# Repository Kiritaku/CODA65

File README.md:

# CODA65
 A 65% keyboard with split arrow keys, rotary encoder, and underglow

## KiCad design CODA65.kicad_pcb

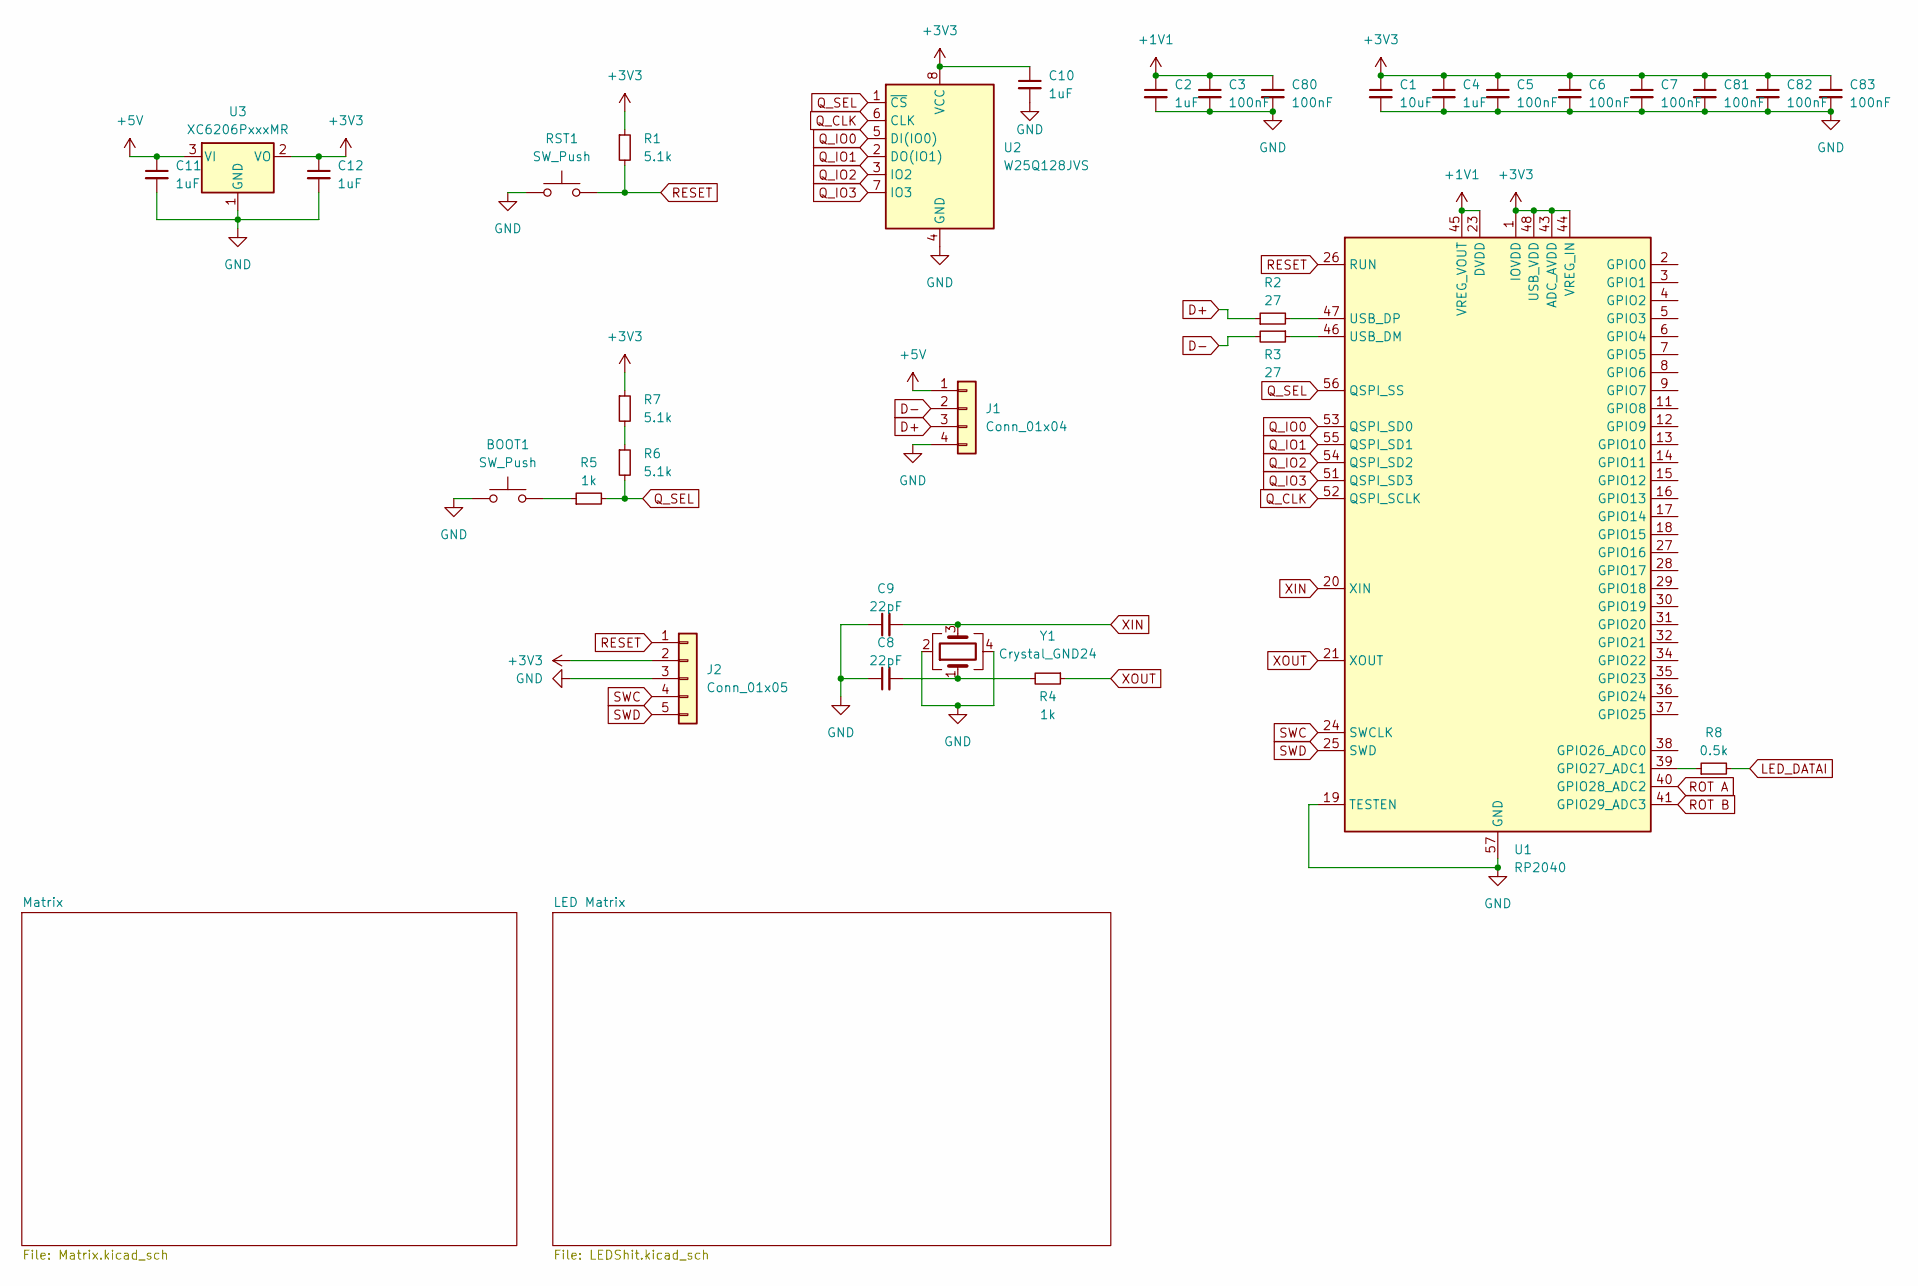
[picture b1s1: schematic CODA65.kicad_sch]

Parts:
BOOT1: SW_Push; SW_Push_1P1T_XKB_TS-1187A
C1: 10uF; C_0603_1608Metric
C2, C4, C10, C11, C12: 1uF; C_0402_1005Metric
C3, C5, C6, C7, C80, C81, C82, C83: 100nF; C_0402_1005Metric
C8, C9: 22pF; C_0402_1005Metric
J1: Conn_01x04; JST_SH_SM04B-SRSS-TB_1x04-1MP_P1.00mm_Horizontal
J2: Conn_01x05; PinHeader_1x05_P2.54mm_Vertical
R1, R6, R7: 5.1k; R_0402_1005Metric
R2, R3: 27; R_0402_1005Metric
R4, R5: 1k; R_0402_1005Metric
R8: 0.5k; R_0402_1005Metric
RST1: SW_Push; SW_Push_1P1T_XKB_TS-1187A
U1: RP2040; QFN-56-1EP_7x7mm_P0.4mm_EP3.2x3.2mm
U2: W25Q128JVS; SOIC-8_5.23x5.23mm_P1.27mm
U3: XC6206PxxxMR; SOT-23-3
Y1: Crystal_GND24; Crystal_SMD_3225-4Pin_3.2x2.5mm

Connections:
+1V1: C2.1, C3.1, C80.1, U1.23 (DVDD), U1.45 (VREG_VOUT), U1.50 (DVDD)
+3V3: C1.1, C4.1, C5.1, C6.1, C7.1, C10.1, C12.1, C81.1, C82.1, C83.1, J2.2, R1.1, R7.1, U1.1 (IOVDD), U1.10 (IOVDD), U1.22 (IOVDD), U1.33 (IOVDD), U1.42 (IOVDD), U1.43 (ADC_AVDD), U1.44 (VREG_IN), U1.48 (USB_VDD), U1.49 (IOVDD), U2.8 (VCC), U3.2 (VO)
+5V: C11.1, J1.1, U3.3 (VI); also elsewhere on the board
D+: J1.3, R2.1
D-: J1.2, R3.2
GND: BOOT1.1, C1.2, C2.2, C3.2, C4.2, C5.2, C6.2, C7.2, C8.1, C9.1, C10.2, C11.2, C12.2, C80.2, C81.2, C82.2, C83.2, J1.4, J2.3, RST1.1, U1.19 (TESTEN), U1.57 (GND), U2.4 (GND), U3.1 (GND), Y1.2, Y1.4; also elsewhere on the board
LED_DATAI: R8.2; also elsewhere on the board
unnamed: BOOT1.2, R5.1
unnamed: C8.2, R4.2, Y1.1
unnamed: R6.1, R7.2
unnamed: R8.1, U1.39 (GPIO27_ADC1)
unnamed: R3.1, U1.46 (USB_DM)
unnamed: R2.2, U1.47 (USB_DP)
Q_CLK: U1.52 (QSPI_SCLK), U2.6 (CLK)
Q_IO0: U1.53 (QSPI_SD0), U2.5 (DI(IO0))
Q_IO1: U1.55 (QSPI_SD1), U2.2 (DO(IO1))
Q_IO2: U1.54 (QSPI_SD2), U2.3 (IO2)
Q_IO3: U1.51 (QSPI_SD3), U2.7 (IO3)
Q_SEL: R5.2, R6.2, U1.56 (QSPI_SS), U2.1 (~CS)
RESET: J2.1, R1.2, RST1.2, U1.26 (RUN)
ROT A: U1.40 (GPIO28_ADC2); also elsewhere on the board
ROT B: U1.41 (GPIO29_ADC3); also elsewhere on the board
SWC: J2.4, U1.24 (SWCLK)
SWD: J2.5, U1.25 (SWD)
XIN: C9.2, U1.20 (XIN), Y1.3
XOUT: R4.1, U1.21 (XOUT)

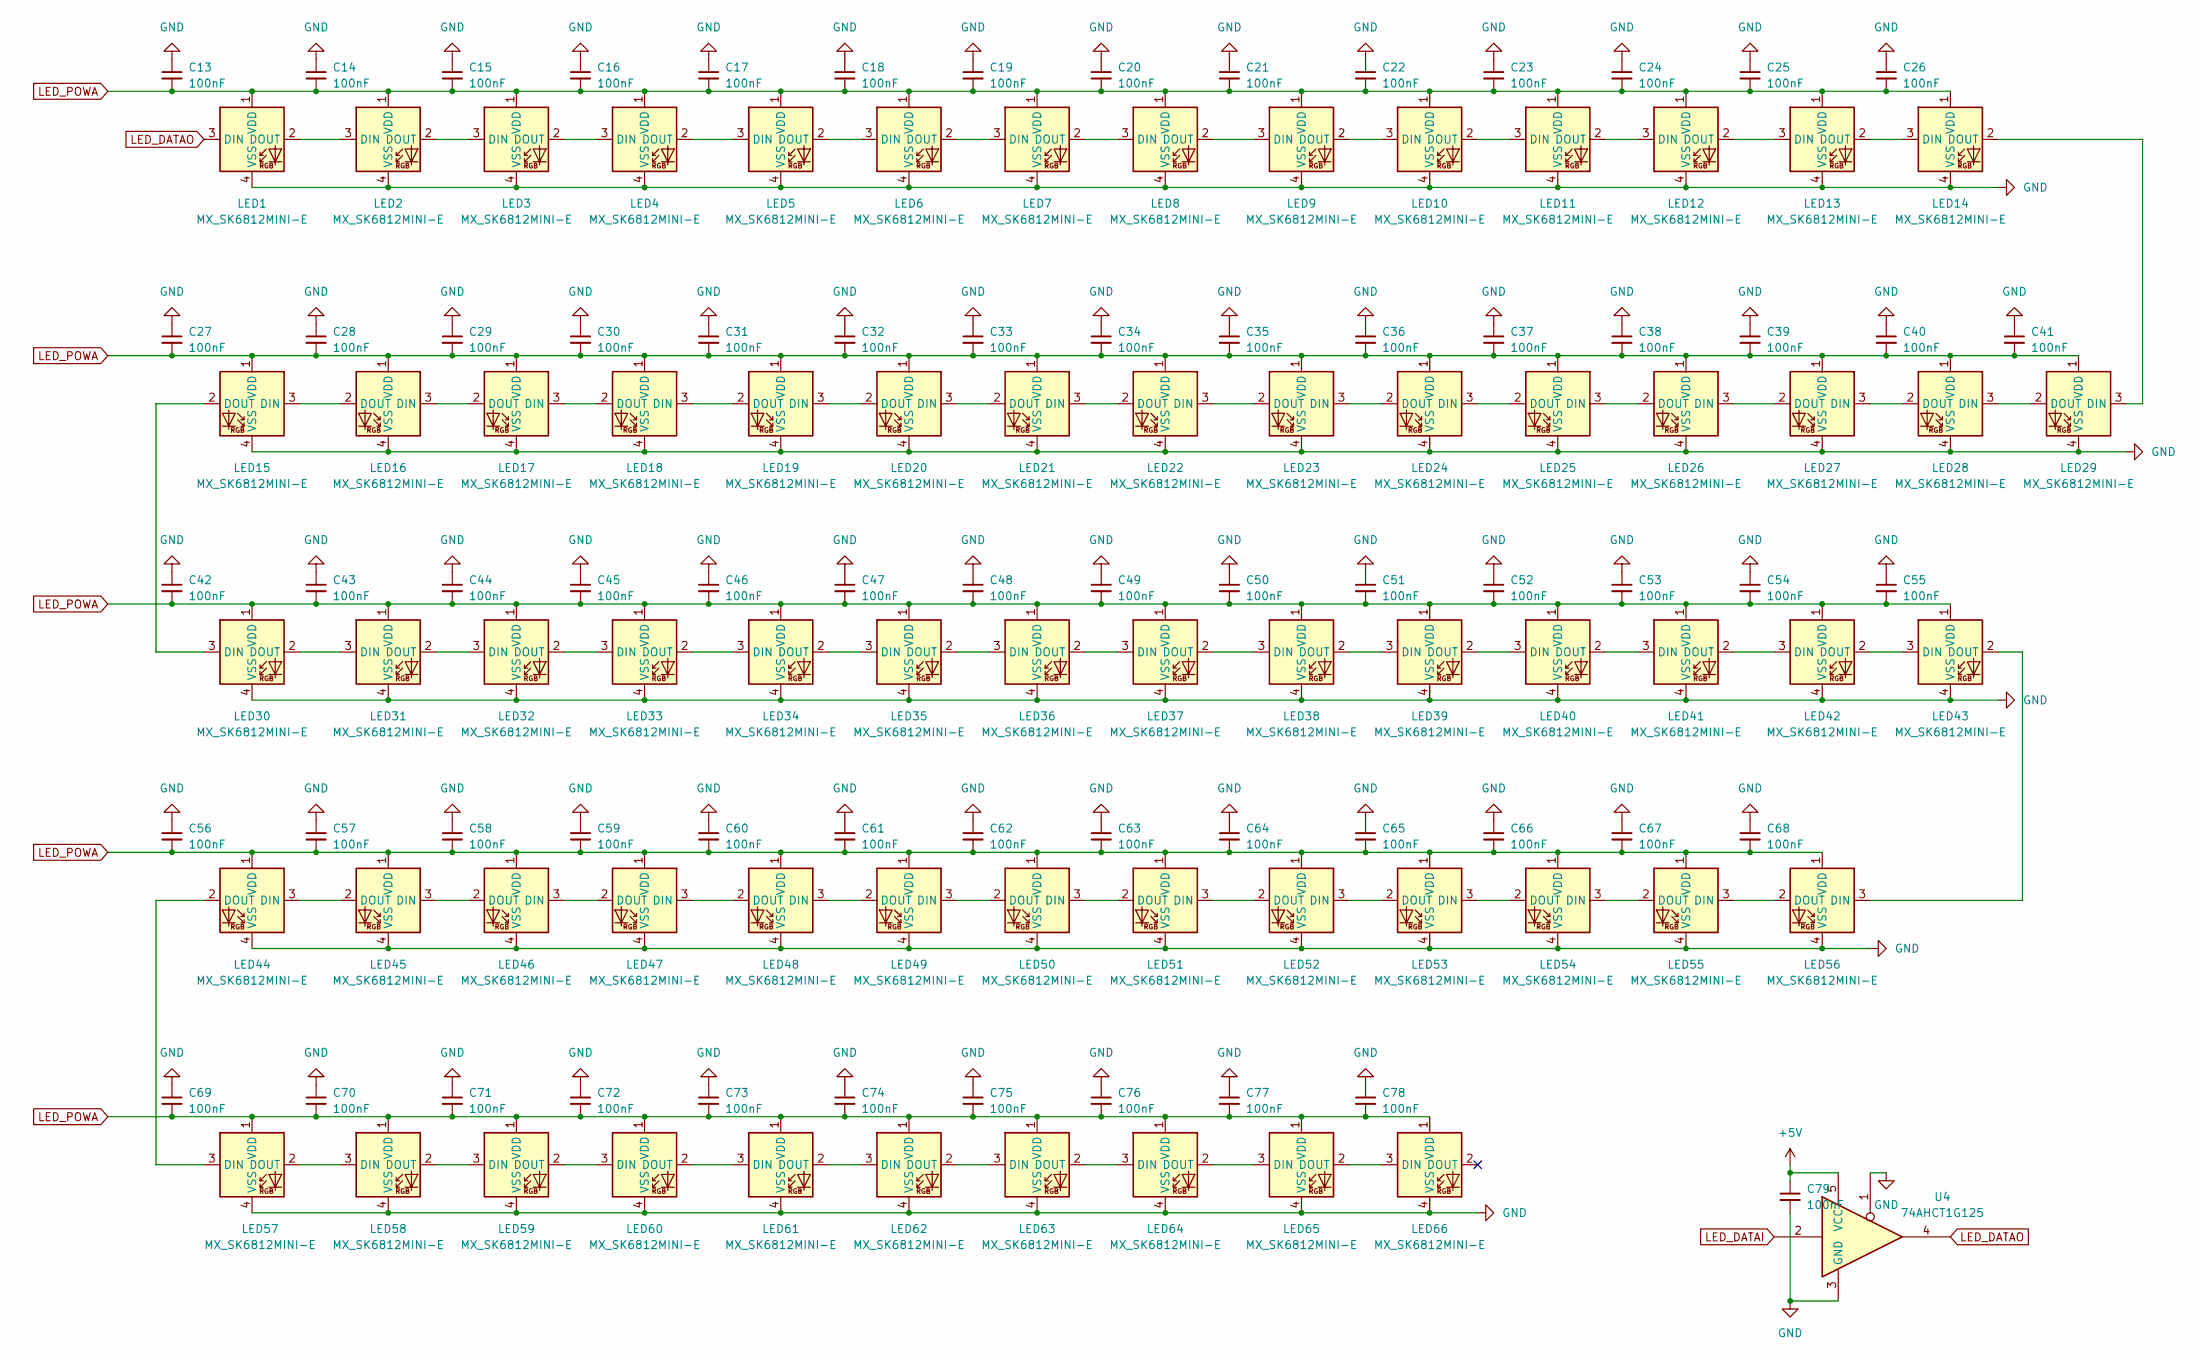
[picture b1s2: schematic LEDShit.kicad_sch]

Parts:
C13, C14, C15, C16, C17, C18, C19, C20, C21, C22, C23, C24, C25, C26, C27, C28, C29, C30, C31, C32, C33, C34, C35, C36, C37, C38, C39, C40, C41, C42, C43, C44, C45, C46, C47, C48, C49, C50, C51, C52, C53, C54, C55, C56, C57, C58, C59, C60, C61, C62, C63, C64, C65, C66, C67, C68, C69, C70, C71, C72, C73, C74, C75, C76, C77, C78, C79: 100nF; C_0402_1005Metric
LED1, LED2, LED3, LED4, LED5, LED6, LED7, LED8, LED9, LED10, LED11, LED12, LED13, LED14, LED15, LED16, LED17, LED18, LED19, LED20, LED21, LED22, LED23, LED24, LED25, LED26, LED27, LED28, LED29, LED30, LED31, LED32, LED33, LED34, LED35, LED36, LED37, LED38, LED39, LED40, LED41, LED42, LED43, LED44, LED45, LED46, LED47, LED48, LED49, LED50, LED51, LED52, LED53, LED54, LED55, LED56, LED57, LED58, LED59, LED60, LED61, LED62, LED63, LED64, LED65, LED66: MX_SK6812MINI-E; LED_MX_6028R
U4: 74AHCT1G125; SOT-23-5

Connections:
+5V: C79.1, U4.5 (VCC); also elsewhere on the board
GND: C13.1, C14.1, C15.1, C16.1, C17.1, C18.1, C19.1, C20.1, C21.1, C22.1, C23.1, C24.1, C25.1, C26.1, C27.1, C28.1, C29.1, C30.1, C31.1, C32.1, C33.1, C34.1, C35.1, C36.1, C37.1, C38.1, C39.1, C40.1, C41.1, C42.1, C43.1, C44.1, C45.1, C46.1, C47.1, C48.1, C49.1, C50.1, C51.1, C52.1, C53.1, C54.1, C55.1, C56.1, C57.1, C58.1, C59.1, C60.1, C61.1, C62.1, C63.1, C64.1, C65.1, C66.1, C67.1, C68.1, C69.1, C70.1, C71.1, C72.1, C73.1, C74.1, C75.1, C76.1, C77.1, C78.1, C79.2, LED1.4 (VSS), LED2.4 (VSS), LED3.4 (VSS), LED4.4 (VSS), LED5.4 (VSS), LED6.4 (VSS), LED7.4 (VSS), LED8.4 (VSS), LED9.4 (VSS), LED10.4 (VSS), LED11.4 (VSS), LED12.4 (VSS), LED13.4 (VSS), LED14.4 (VSS), LED15.4 (VSS), LED16.4 (VSS), LED17.4 (VSS), LED18.4 (VSS), LED19.4 (VSS), LED20.4 (VSS), LED21.4 (VSS), LED22.4 (VSS), LED23.4 (VSS), LED24.4 (VSS), LED25.4 (VSS), LED26.4 (VSS), LED27.4 (VSS), LED28.4 (VSS), LED29.4 (VSS), LED30.4 (VSS), LED31.4 (VSS), LED32.4 (VSS), LED33.4 (VSS), LED34.4 (VSS), LED35.4 (VSS), LED36.4 (VSS), LED37.4 (VSS), LED38.4 (VSS), LED39.4 (VSS), LED40.4 (VSS), LED41.4 (VSS), LED42.4 (VSS), LED43.4 (VSS), LED44.4 (VSS), LED45.4 (VSS), LED46.4 (VSS), LED47.4 (VSS), LED48.4 (VSS), LED49.4 (VSS), LED50.4 (VSS), LED51.4 (VSS), LED52.4 (VSS), LED53.4 (VSS), LED54.4 (VSS), LED55.4 (VSS), LED56.4 (VSS), LED57.4 (VSS), LED58.4 (VSS), LED59.4 (VSS), LED60.4 (VSS), LED61.4 (VSS), LED62.4 (VSS), LED63.4 (VSS), LED64.4 (VSS), LED65.4 (VSS), LED66.4 (VSS), U4.1, U4.3 (GND); also elsewhere on the board
LED_DATAI: U4.2; also elsewhere on the board
LED_DATAO: LED1.3 (DIN), U4.4
LED_POWA: C13.2, C14.2, C15.2, C16.2, C17.2, C18.2, C19.2, C20.2, C21.2, C22.2, C23.2, C24.2, C25.2, C26.2, C27.2, C28.2, C29.2, C30.2, C31.2, C32.2, C33.2, C34.2, C35.2, C36.2, C37.2, C38.2, C39.2, C40.2, C41.2, C42.2, C43.2, C44.2, C45.2, C46.2, C47.2, C48.2, C49.2, C50.2, C51.2, C52.2, C53.2, C54.2, C55.2, C56.2, C57.2, C58.2, C59.2, C60.2, C61.2, C62.2, C63.2, C64.2, C65.2, C66.2, C67.2, C68.2, C69.2, C70.2, C71.2, C72.2, C73.2, C74.2, C75.2, C76.2, C77.2, C78.2, LED1.1 (VDD), LED2.1 (VDD), LED3.1 (VDD), LED4.1 (VDD), LED5.1 (VDD), LED6.1 (VDD), LED7.1 (VDD), LED8.1 (VDD), LED9.1 (VDD), LED10.1 (VDD), LED11.1 (VDD), LED12.1 (VDD), LED13.1 (VDD), LED14.1 (VDD), LED15.1 (VDD), LED16.1 (VDD), LED17.1 (VDD), LED18.1 (VDD), LED19.1 (VDD), LED20.1 (VDD), LED21.1 (VDD), LED22.1 (VDD), LED23.1 (VDD), LED24.1 (VDD), LED25.1 (VDD), LED26.1 (VDD), LED27.1 (VDD), LED28.1 (VDD), LED29.1 (VDD), LED30.1 (VDD), LED31.1 (VDD), LED32.1 (VDD), LED33.1 (VDD), LED34.1 (VDD), LED35.1 (VDD), LED36.1 (VDD), LED37.1 (VDD), LED38.1 (VDD), LED39.1 (VDD), LED40.1 (VDD), LED41.1 (VDD), LED42.1 (VDD), LED43.1 (VDD), LED44.1 (VDD), LED45.1 (VDD), LED46.1 (VDD), LED47.1 (VDD), LED48.1 (VDD), LED49.1 (VDD), LED50.1 (VDD), LED51.1 (VDD), LED52.1 (VDD), LED53.1 (VDD), LED54.1 (VDD), LED55.1 (VDD), LED56.1 (VDD), LED57.1 (VDD), LED58.1 (VDD), LED59.1 (VDD), LED60.1 (VDD), LED61.1 (VDD), LED62.1 (VDD), LED63.1 (VDD), LED64.1 (VDD), LED65.1 (VDD), LED66.1 (VDD)
unnamed: LED1.2 (DOUT), LED2.3 (DIN)
unnamed: LED2.2 (DOUT), LED3.3 (DIN)
unnamed: LED3.2 (DOUT), LED4.3 (DIN)
unnamed: LED4.2 (DOUT), LED5.3 (DIN)
unnamed: LED5.2 (DOUT), LED6.3 (DIN)
unnamed: LED6.2 (DOUT), LED7.3 (DIN)
unnamed: LED7.2 (DOUT), LED8.3 (DIN)
unnamed: LED8.2 (DOUT), LED9.3 (DIN)
unnamed: LED9.2 (DOUT), LED10.3 (DIN)
unnamed: LED10.2 (DOUT), LED11.3 (DIN)
unnamed: LED11.2 (DOUT), LED12.3 (DIN)
unnamed: LED12.2 (DOUT), LED13.3 (DIN)
unnamed: LED13.2 (DOUT), LED14.3 (DIN)
unnamed: LED14.2 (DOUT), LED29.3 (DIN)
unnamed: LED15.3 (DIN), LED16.2 (DOUT)
unnamed: LED15.2 (DOUT), LED30.3 (DIN)
unnamed: LED16.3 (DIN), LED17.2 (DOUT)
unnamed: LED17.3 (DIN), LED18.2 (DOUT)
unnamed: LED18.3 (DIN), LED19.2 (DOUT)
unnamed: LED19.3 (DIN), LED20.2 (DOUT)
unnamed: LED20.3 (DIN), LED21.2 (DOUT)
unnamed: LED21.3 (DIN), LED22.2 (DOUT)
unnamed: LED22.3 (DIN), LED23.2 (DOUT)
unnamed: LED23.3 (DIN), LED24.2 (DOUT)
unnamed: LED24.3 (DIN), LED25.2 (DOUT)
unnamed: LED25.3 (DIN), LED26.2 (DOUT)
unnamed: LED26.3 (DIN), LED27.2 (DOUT)
unnamed: LED27.3 (DIN), LED28.2 (DOUT)
unnamed: LED28.3 (DIN), LED29.2 (DOUT)
unnamed: LED30.2 (DOUT), LED31.3 (DIN)
unnamed: LED31.2 (DOUT), LED32.3 (DIN)
unnamed: LED32.2 (DOUT), LED33.3 (DIN)
unnamed: LED33.2 (DOUT), LED34.3 (DIN)
unnamed: LED34.2 (DOUT), LED35.3 (DIN)
unnamed: LED35.2 (DOUT), LED36.3 (DIN)
unnamed: LED36.2 (DOUT), LED37.3 (DIN)
unnamed: LED37.2 (DOUT), LED38.3 (DIN)
unnamed: LED38.2 (DOUT), LED39.3 (DIN)
unnamed: LED39.2 (DOUT), LED40.3 (DIN)
unnamed: LED40.2 (DOUT), LED41.3 (DIN)
unnamed: LED41.2 (DOUT), LED42.3 (DIN)
unnamed: LED42.2 (DOUT), LED43.3 (DIN)
unnamed: LED43.2 (DOUT), LED56.3 (DIN)
unnamed: LED44.3 (DIN), LED45.2 (DOUT)
unnamed: LED44.2 (DOUT), LED57.3 (DIN)
unnamed: LED45.3 (DIN), LED46.2 (DOUT)
unnamed: LED46.3 (DIN), LED47.2 (DOUT)
unnamed: LED47.3 (DIN), LED48.2 (DOUT)
unnamed: LED48.3 (DIN), LED49.2 (DOUT)
unnamed: LED49.3 (DIN), LED50.2 (DOUT)
unnamed: LED50.3 (DIN), LED51.2 (DOUT)
unnamed: LED51.3 (DIN), LED52.2 (DOUT)
unnamed: LED52.3 (DIN), LED53.2 (DOUT)
unnamed: LED53.3 (DIN), LED54.2 (DOUT)
unnamed: LED54.3 (DIN), LED55.2 (DOUT)
unnamed: LED55.3 (DIN), LED56.2 (DOUT)
unnamed: LED57.2 (DOUT), LED58.3 (DIN)
unnamed: LED58.2 (DOUT), LED59.3 (DIN)
unnamed: LED59.2 (DOUT), LED60.3 (DIN)
unnamed: LED60.2 (DOUT), LED61.3 (DIN)
unnamed: LED61.2 (DOUT), LED62.3 (DIN)
unnamed: LED62.2 (DOUT), LED63.3 (DIN)
unnamed: LED63.2 (DOUT), LED64.3 (DIN)
unnamed: LED64.2 (DOUT), LED65.3 (DIN)
unnamed: LED65.2 (DOUT), LED66.3 (DIN)

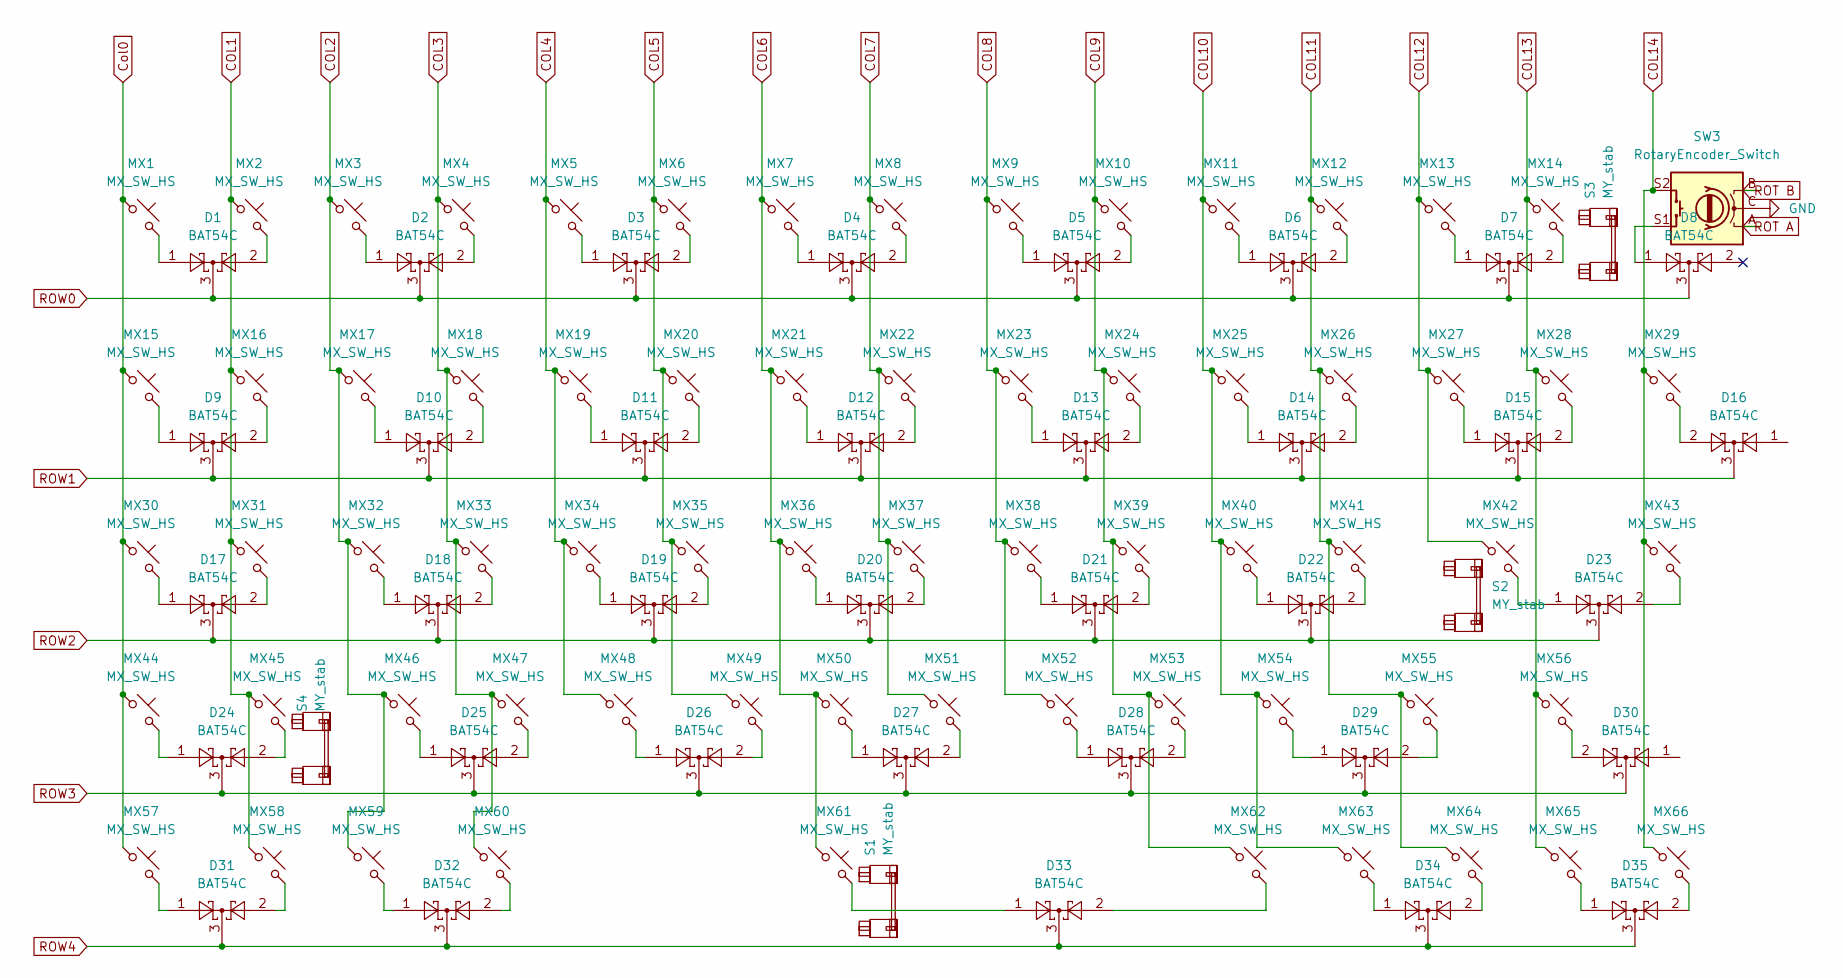
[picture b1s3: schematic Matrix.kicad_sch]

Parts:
D1, D2, D3, D4, D5, D6, D7, D8, D9, D10, D11, D12, D13, D14, D15, D16, D17, D18, D19, D20, D21, D22, D23, D24, D25, D26, D27, D28, D29, D30, D31, D32, D33, D34, D35: BAT54C; SOT-23
MX1, MX2, MX3, MX4, MX5, MX6, MX7, MX8, MX9, MX10, MX11, MX12, MX13, MX14, MX16, MX17, MX18, MX19, MX20, MX21, MX22, MX23, MX24, MX25, MX26, MX27, MX29, MX31, MX32, MX33, MX34, MX35, MX36, MX37, MX38, MX39, MX40, MX41, MX42, MX43, MX44, MX45, MX46, MX47, MX48, MX49, MX50, MX51, MX52, MX53, MX54, MX56, MX57, MX59, MX60, MX61, MX62, MX64, MX65, MX66: MX_SW_HS; SW_MX_HS_1u
MX15, MX28: MX_SW_HS; SW_MX_HS_1.5u
MX30, MX55: MX_SW_HS; SW_MX_HS_1.75u
MX58, MX63: MX_SW_HS; SW_MX_HS_1.25u
S1: MY_stab; STAB_MX_P_6.25u
S2, S4: MY_stab; STAB_MX_P_2.25u
S3: MY_stab; STAB_MX_P_2u
SW3: RotaryEncoder_Switch; RotaryEncoder_Alps_EC11E-Switch_Vertical_H20mm

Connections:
COL1: MX2.1, MX16.1, MX31.1, MX45.1, MX58.1
COL2: MX3.1, MX17.1, MX32.1, MX46.1, MX59.1
COL3: MX4.1, MX18.1, MX33.1, MX47.1, MX60.1
COL4: MX5.1, MX19.1, MX34.1, MX48.1
COL5: MX6.1, MX20.1, MX35.1, MX49.1
COL6: MX7.1, MX21.1, MX36.1, MX50.1, MX61.1
COL7: MX8.1, MX22.1, MX37.1, MX51.1
COL8: MX9.1, MX23.1, MX38.1, MX52.1
COL9: MX10.1, MX24.1, MX39.1, MX53.1, MX62.1
COL10: MX11.1, MX25.1, MX40.1, MX54.1, MX63.1
COL11: MX12.1, MX26.1, MX41.1, MX55.1, MX64.1
COL12: MX13.1, MX27.1, MX42.1
COL13: MX14.1, MX28.1, MX56.1, MX65.1
COL14: MX29.1, MX43.1, MX66.1, SW3.S2
Col0: MX1.1, MX15.1, MX30.1, MX44.1, MX57.1
GND: SW3.C; also elsewhere on the board
unnamed: D1.1, MX1.2
unnamed: D1.2, MX2.2
unnamed: D2.1, MX3.2
unnamed: D2.2, MX4.2
unnamed: D3.1, MX5.2
unnamed: D3.2, MX6.2
unnamed: D4.1, MX7.2
unnamed: D4.2, MX8.2
unnamed: D5.1, MX9.2
unnamed: D5.2, MX10.2
unnamed: D6.1, MX11.2
unnamed: D6.2, MX12.2
unnamed: D7.1, MX13.2
unnamed: D7.2, MX14.2
unnamed: D8.1, SW3.S1
unnamed: D9.1, MX15.2
unnamed: D9.2, MX16.2
unnamed: D10.1, MX17.2
unnamed: D10.2, MX18.2
unnamed: D11.1, MX19.2
unnamed: D11.2, MX20.2
unnamed: D12.1, MX21.2
unnamed: D12.2, MX22.2
unnamed: D13.1, MX23.2
unnamed: D13.2, MX24.2
unnamed: D14.1, MX25.2
unnamed: D14.2, MX26.2
unnamed: D15.1, MX27.2
unnamed: D15.2, MX28.2
unnamed: D16.2, MX29.2
unnamed: D17.1, MX30.2
unnamed: D17.2, MX31.2
unnamed: D18.1, MX32.2
unnamed: D18.2, MX33.2
unnamed: D19.1, MX34.2
unnamed: D19.2, MX35.2
unnamed: D20.1, MX36.2
unnamed: D20.2, MX37.2
unnamed: D21.1, MX38.2
unnamed: D21.2, MX39.2
unnamed: D22.1, MX40.2
unnamed: D22.2, MX41.2
unnamed: D23.1, MX42.2
unnamed: D23.2, MX43.2
unnamed: D24.1, MX44.2
unnamed: D24.2, MX45.2
unnamed: D25.1, MX46.2
unnamed: D25.2, MX47.2
unnamed: D26.1, MX48.2
unnamed: D26.2, MX49.2
unnamed: D27.1, MX50.2
unnamed: D27.2, MX51.2
unnamed: D28.1, MX52.2
unnamed: D28.2, MX53.2
unnamed: D29.1, MX54.2
unnamed: D29.2, MX55.2
unnamed: D30.2, MX56.2
unnamed: D31.1, MX57.2
unnamed: D31.2, MX58.2
unnamed: D32.1, MX59.2
unnamed: D32.2, MX60.2
unnamed: D33.1, MX61.2
unnamed: D33.2, MX62.2
unnamed: D34.1, MX63.2
unnamed: D34.2, MX64.2
unnamed: D35.1, MX65.2
unnamed: D35.2, MX66.2
ROT A: SW3.A; also elsewhere on the board
ROT B: SW3.B; also elsewhere on the board
ROW0: D1.3, D2.3, D3.3, D4.3, D5.3, D6.3, D7.3, D8.3
ROW1: D9.3, D10.3, D11.3, D12.3, D13.3, D14.3, D15.3, D16.3
ROW2: D17.3, D18.3, D19.3, D20.3, D21.3, D22.3, D23.3
ROW3: D24.3, D25.3, D26.3, D27.3, D28.3, D29.3, D30.3
ROW4: D31.3, D32.3, D33.3, D34.3, D35.3

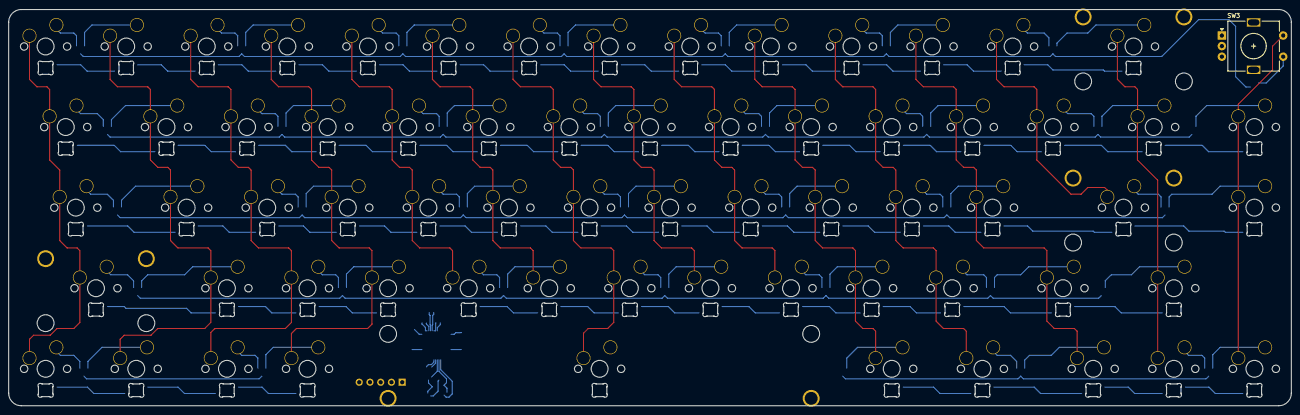
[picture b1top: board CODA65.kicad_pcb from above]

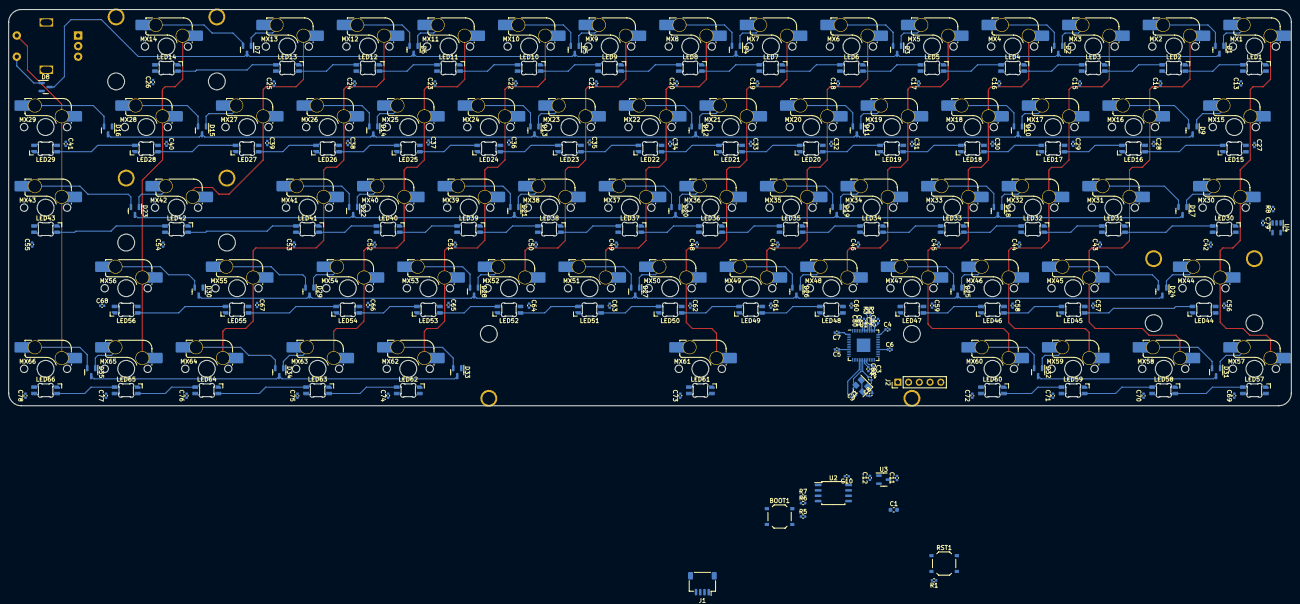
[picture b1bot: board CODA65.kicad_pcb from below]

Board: 2 copper layers, 303.2 x 93.7 mm, 272 parts (267 on the bottom side), 180 nets.

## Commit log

2023-12-28 initialize project
2023-12-28 begin case design
2023-12-29 MCU schematic setup
2023-12-30 Begin matrix schema
    uwu
2023-12-30 Finished switch matrix
2023-12-30 Begin LED matrix
2024-01-06 idk
    dont remember what i changed lol i think it should be led shit
2024-01-18 Led Matrix stuf
    need to get a better idea of power/data reqs
2024-01-19 Finished LED matrix
2024-01-22 assigned schema
2025-02-02 Version Update
    Moved to latest kicad version
2025-02-20 check this later
2025-02-28 small fixes
    flipped pcb, fixed edge cut issue
2025-05-23 Fixes and routing
    Routed Col and Row for switches.
    Fixed annotation of LEDs and caps.
    Started LED matrix Routing.
    Started mcu and supporting routing.
2025-05-23 LED Routing
    LED Data matrix moslty routed out besides home runs.
2025-05-25 Routed more of matrix; Grounded
2025-05-26 Col/Row Routing Updates
2025-05-27 Routing Done
2025-05-27 DRC finished
    some unconnected ground plane violations but as far as I can tell they are not an issue.
2025-05-27 Filename Changes
2025-05-27 made led routing easier to see
